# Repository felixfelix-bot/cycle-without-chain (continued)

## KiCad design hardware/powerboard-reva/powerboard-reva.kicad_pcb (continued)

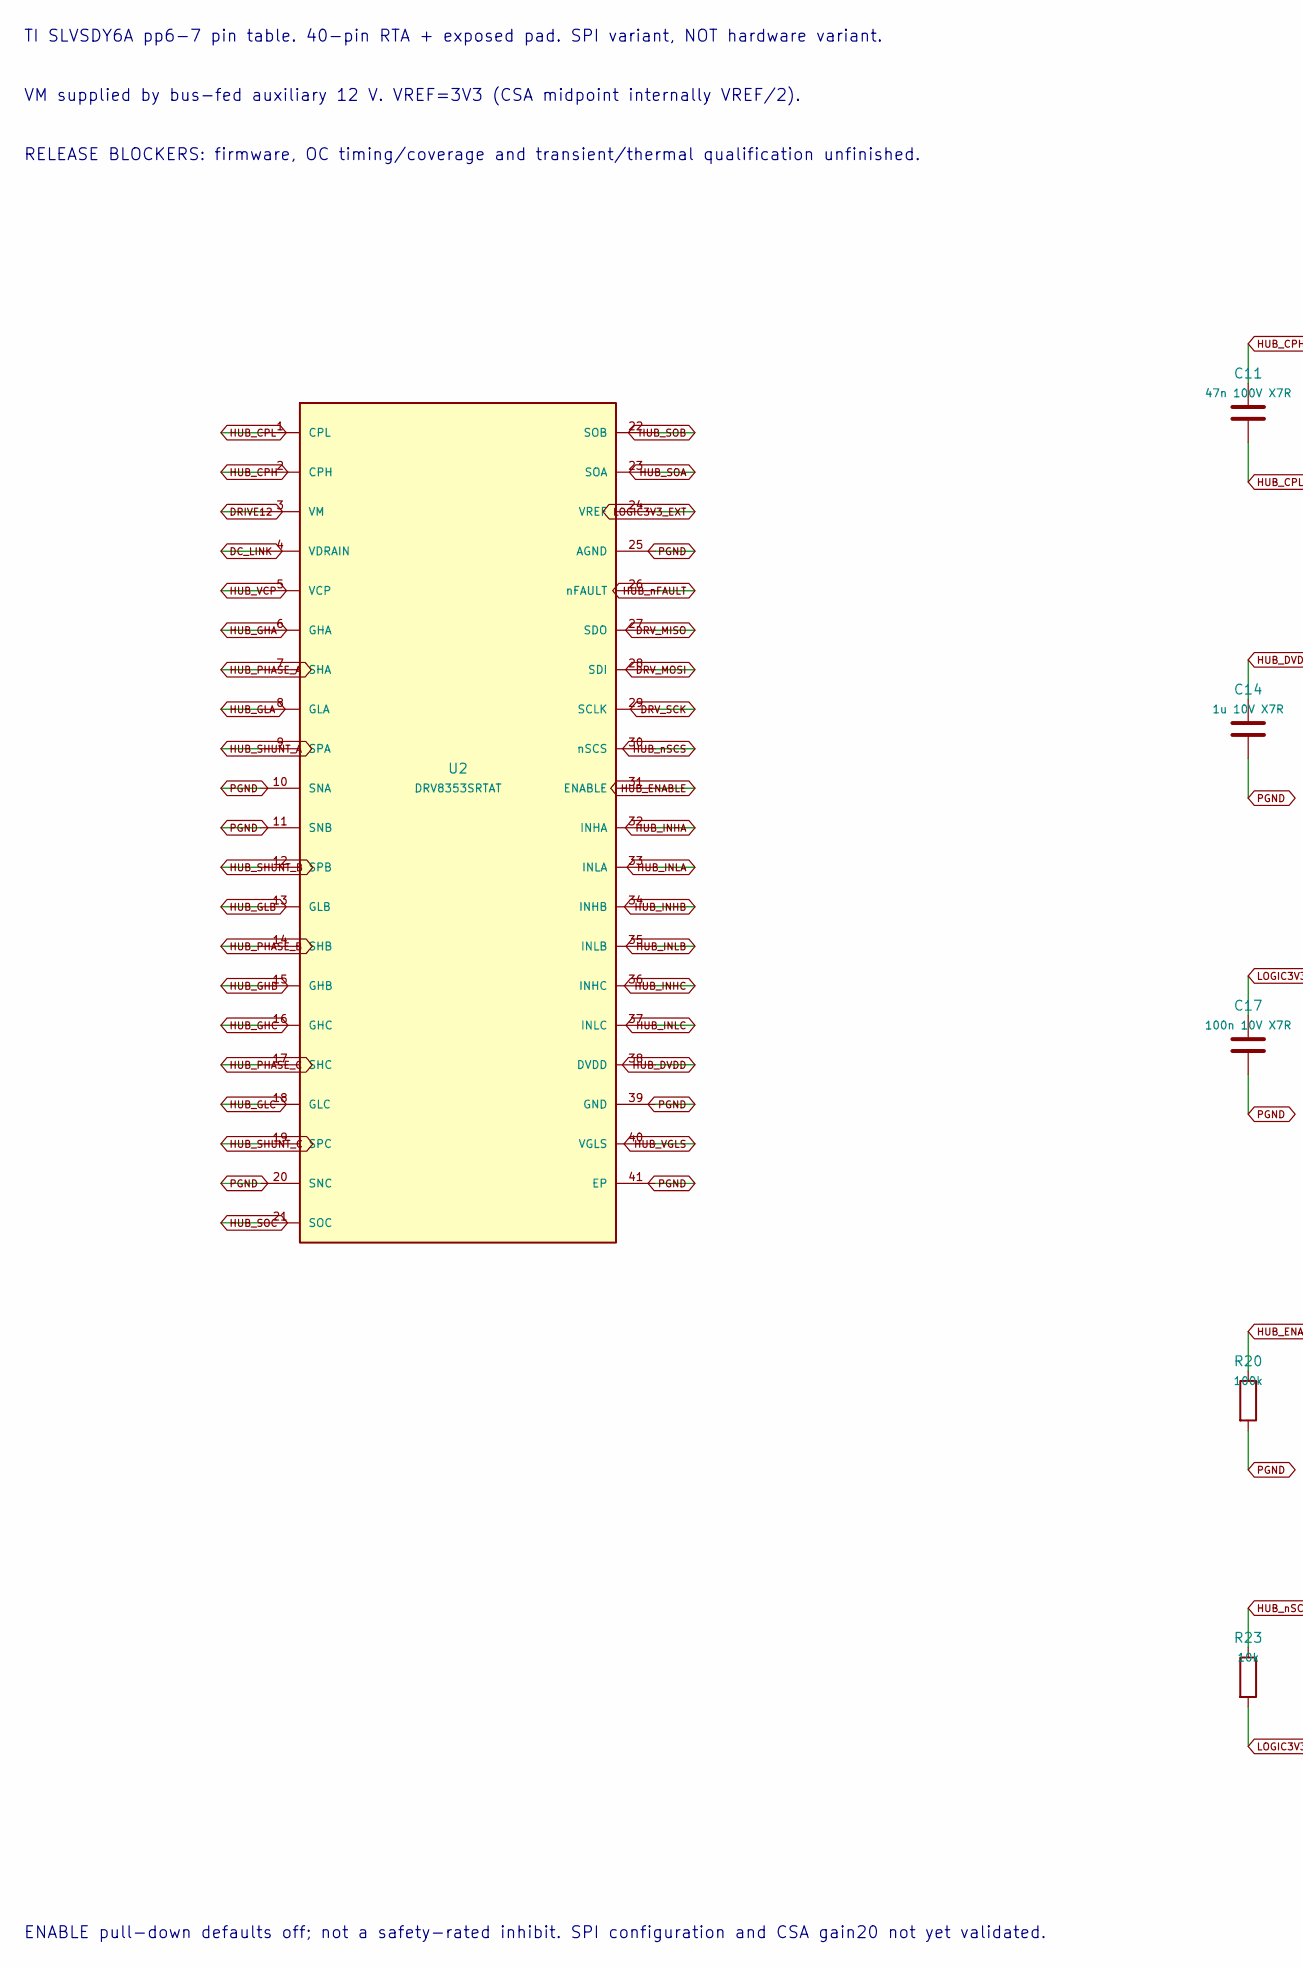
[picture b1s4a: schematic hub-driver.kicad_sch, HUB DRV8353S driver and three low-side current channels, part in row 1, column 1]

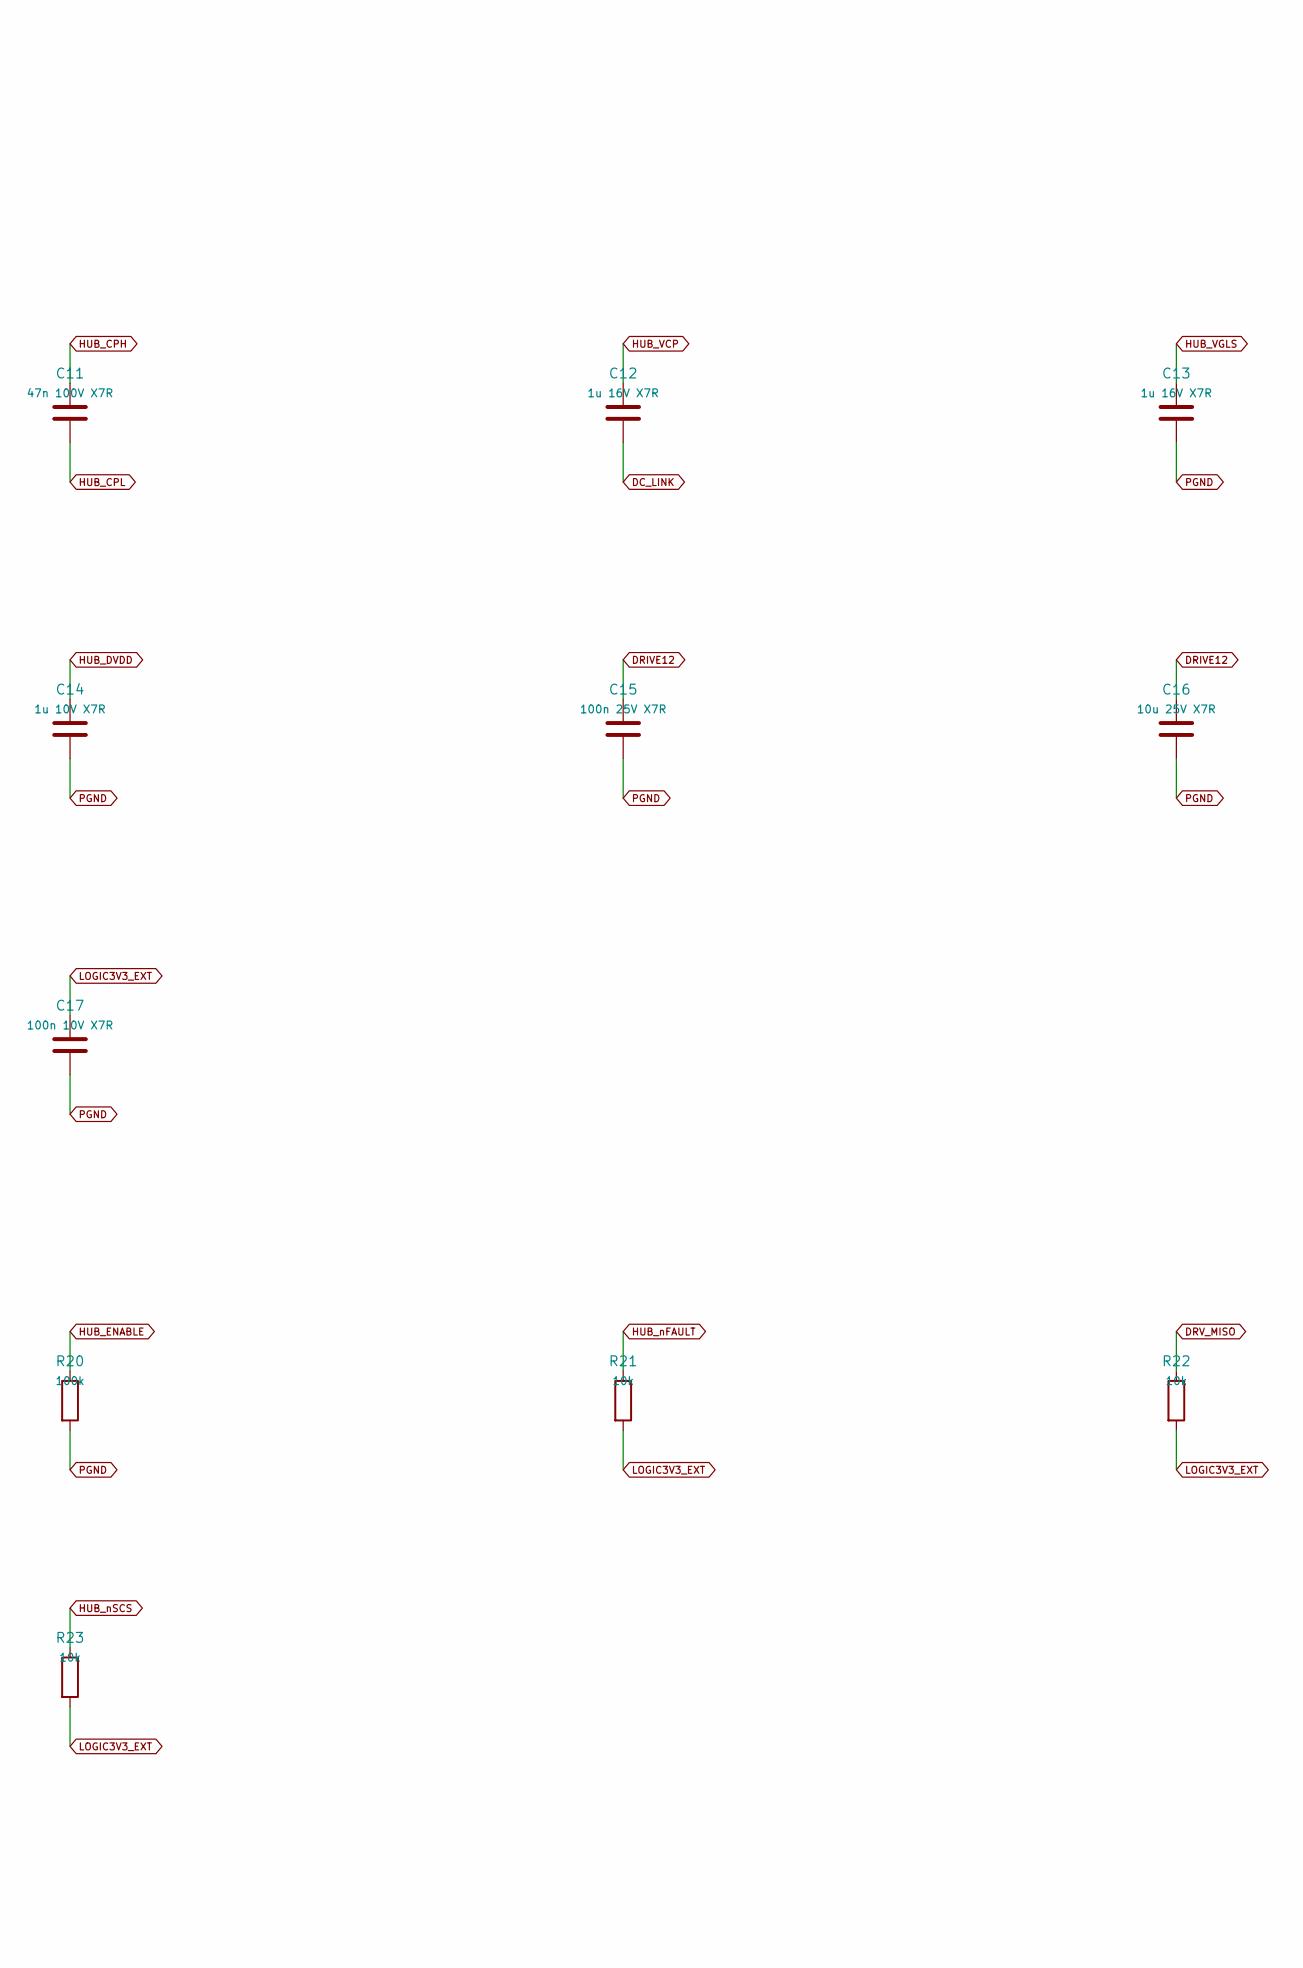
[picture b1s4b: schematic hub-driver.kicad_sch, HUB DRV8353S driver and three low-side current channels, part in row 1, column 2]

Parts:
C11: 47n 100V X7R; C_0805_2012Metric
C12, C13: 1u 16V X7R; C_0805_2012Metric
C14: 1u 10V X7R; C_0603_1608Metric
C15: 100n 25V X7R; C_0805_2012Metric
C16: 10u 25V X7R; C_0805_2012Metric
C17: 100n 10V X7R; C_0603_1608Metric
R20: 100k; R_0805_2012Metric
R21, R22, R23: 10k; R_0805_2012Metric
U2: DRV8353SRTAT; QFN-40-1EP_6x6mm_P0.5mm_EP4.6x4.6mm

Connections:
DC_LINK: C12.2, U2.4 (VDRAIN); also elsewhere on the board
DRIVE12: C15.1, C16.1, U2.3 (VM); also elsewhere on the board
DRV_MISO: R22.1, U2.27 (SDO); also elsewhere on the board
DRV_MOSI: U2.28 (SDI); also elsewhere on the board
DRV_SCK: U2.29 (SCLK); also elsewhere on the board
HUB_CPH: C11.1, U2.2 (CPH)
HUB_CPL: C11.2, U2.1 (CPL)
HUB_DVDD: C14.1, U2.38 (DVDD)
HUB_ENABLE: R20.1, U2.31 (ENABLE); also elsewhere on the board
HUB_GHA: U2.6 (GHA); also elsewhere on the board
HUB_GHB: U2.15 (GHB); also elsewhere on the board
HUB_GHC: U2.16 (GHC); also elsewhere on the board
HUB_GLA: U2.8 (GLA); also elsewhere on the board
HUB_GLB: U2.13 (GLB); also elsewhere on the board
HUB_GLC: U2.18 (GLC); also elsewhere on the board
HUB_INHA: U2.32 (INHA); also elsewhere on the board
HUB_INHB: U2.34 (INHB); also elsewhere on the board
HUB_INHC: U2.36 (INHC); also elsewhere on the board
HUB_INLA: U2.33 (INLA); also elsewhere on the board
HUB_INLB: U2.35 (INLB); also elsewhere on the board
HUB_INLC: U2.37 (INLC); also elsewhere on the board
HUB_PHASE_A: U2.7 (SHA); also elsewhere on the board
HUB_PHASE_B: U2.14 (SHB); also elsewhere on the board
HUB_PHASE_C: U2.17 (SHC); also elsewhere on the board
HUB_SHUNT_A: U2.9 (SPA); also elsewhere on the board
HUB_SHUNT_B: U2.12 (SPB); also elsewhere on the board
HUB_SHUNT_C: U2.19 (SPC); also elsewhere on the board
HUB_SOA: U2.23 (SOA); also elsewhere on the board
HUB_SOB: U2.22 (SOB); also elsewhere on the board
HUB_SOC: U2.21 (SOC); also elsewhere on the board
HUB_VCP: C12.1, U2.5 (VCP)
HUB_VGLS: C13.1, U2.40 (VGLS)
HUB_nFAULT: R21.1, U2.26 (nFAULT); also elsewhere on the board
HUB_nSCS: R23.1, U2.30 (nSCS); also elsewhere on the board
LOGIC3V3_EXT: C17.1, R21.2, R22.2, R23.2, U2.24 (VREF); also elsewhere on the board
PGND: C13.2, C14.2, C15.2, C16.2, C17.2, R20.2, U2.10 (SNA), U2.11 (SNB), U2.20 (SNC), U2.25 (AGND), U2.39 (GND), U2.41 (EP); also elsewhere on the board

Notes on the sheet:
TI SLVSDY6A pp6-7 pin table. 40-pin RTA + exposed pad. SPI variant, NOT hardware variant.
VM supplied by bus-fed auxiliary 12 V. VREF=3V3 (CSA midpoint internally VREF/2).
RELEASE BLOCKERS: firmware, OC timing/coverage and transient/thermal qualification unfinished.
ENABLE pull-down defaults off; not a safety-rated inhibit. SPI configuration and CSA gain20 not yet validated.

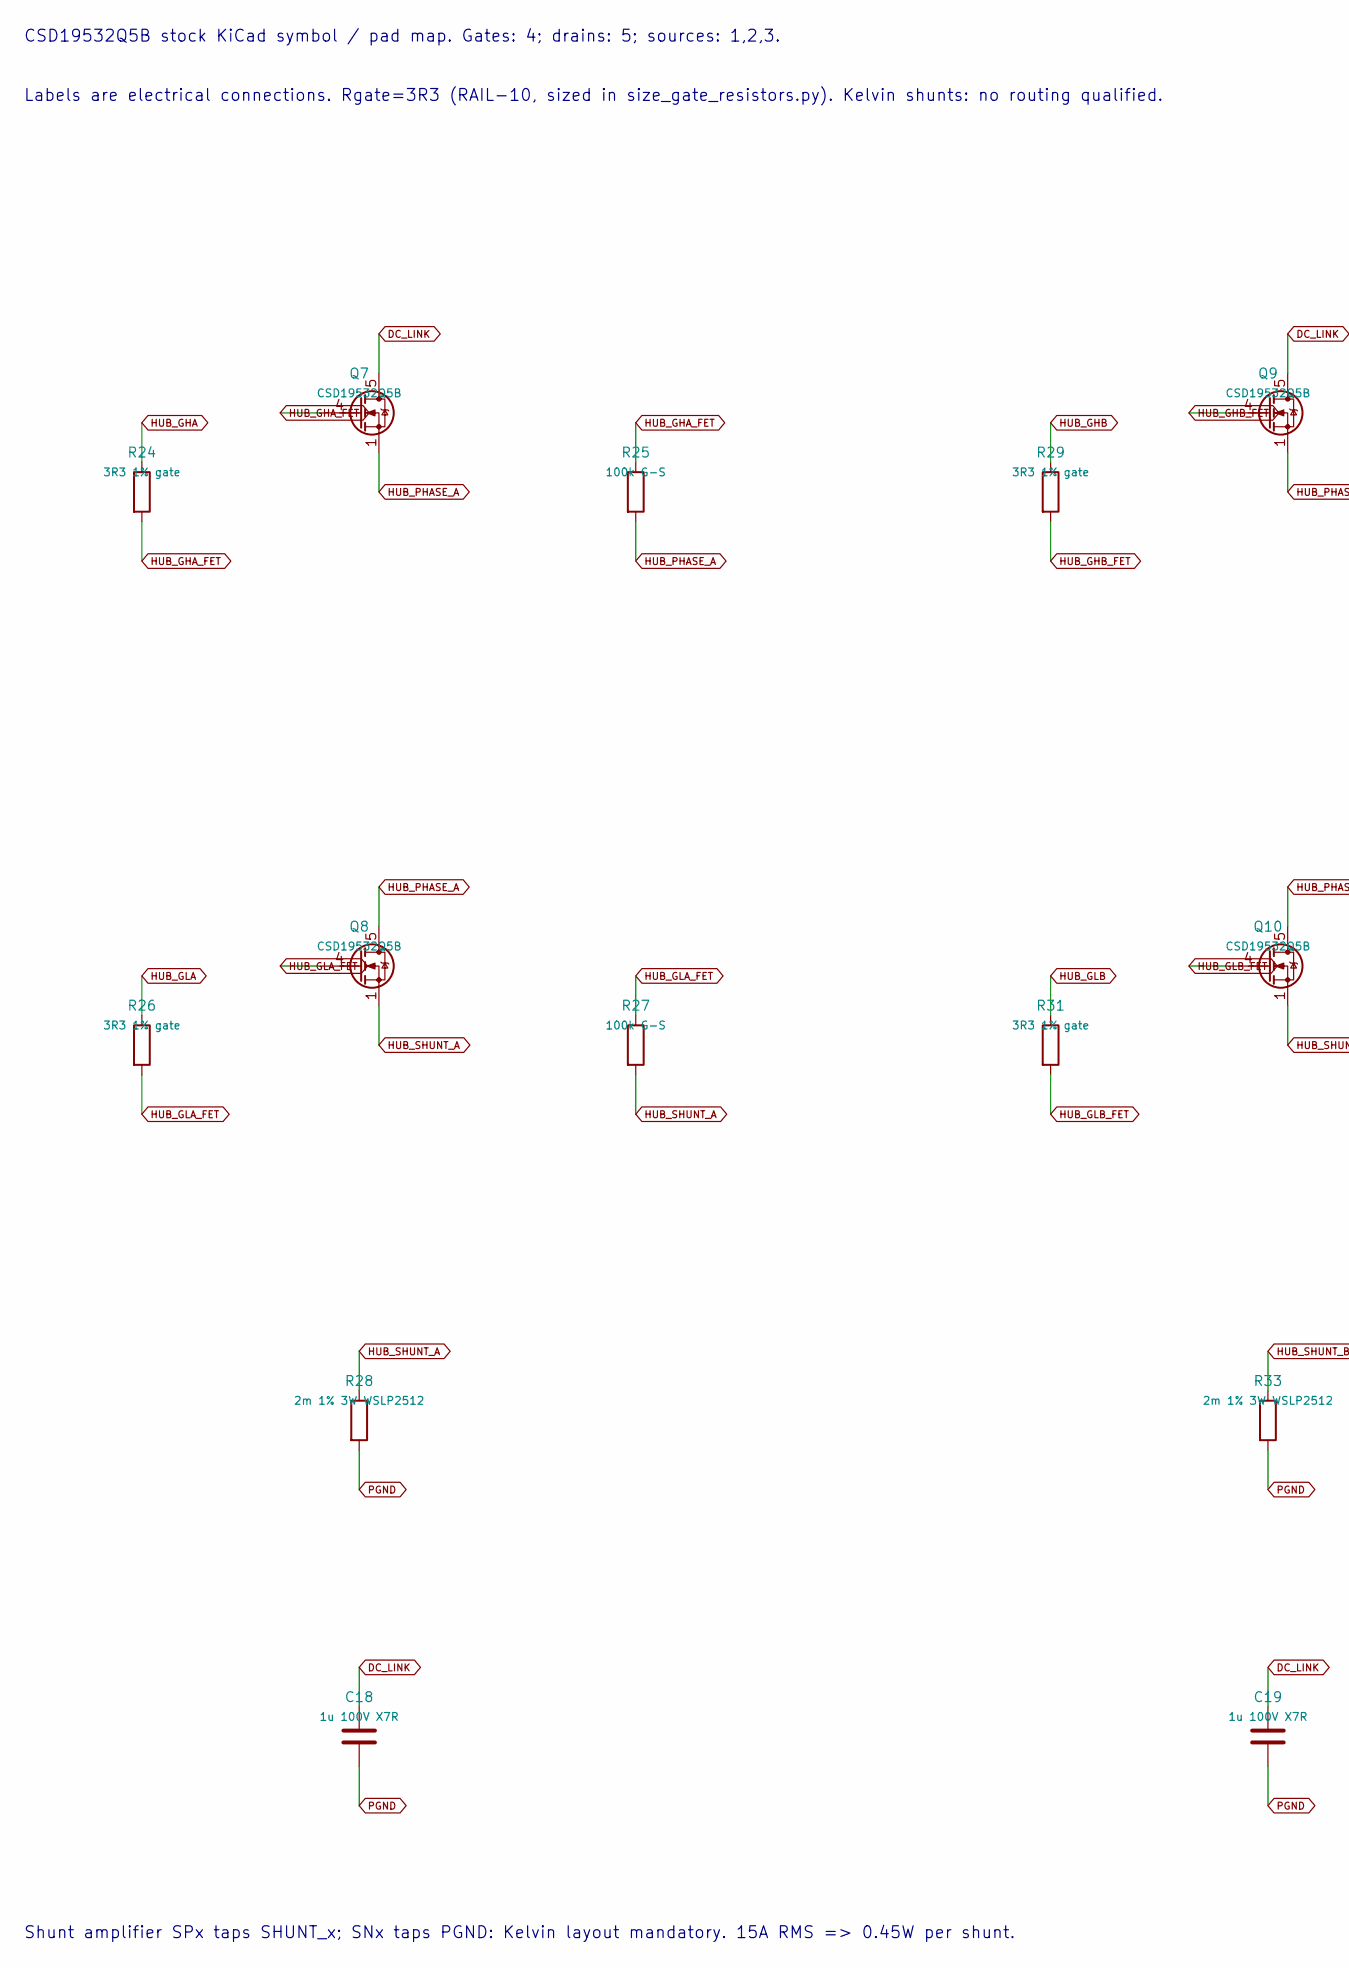
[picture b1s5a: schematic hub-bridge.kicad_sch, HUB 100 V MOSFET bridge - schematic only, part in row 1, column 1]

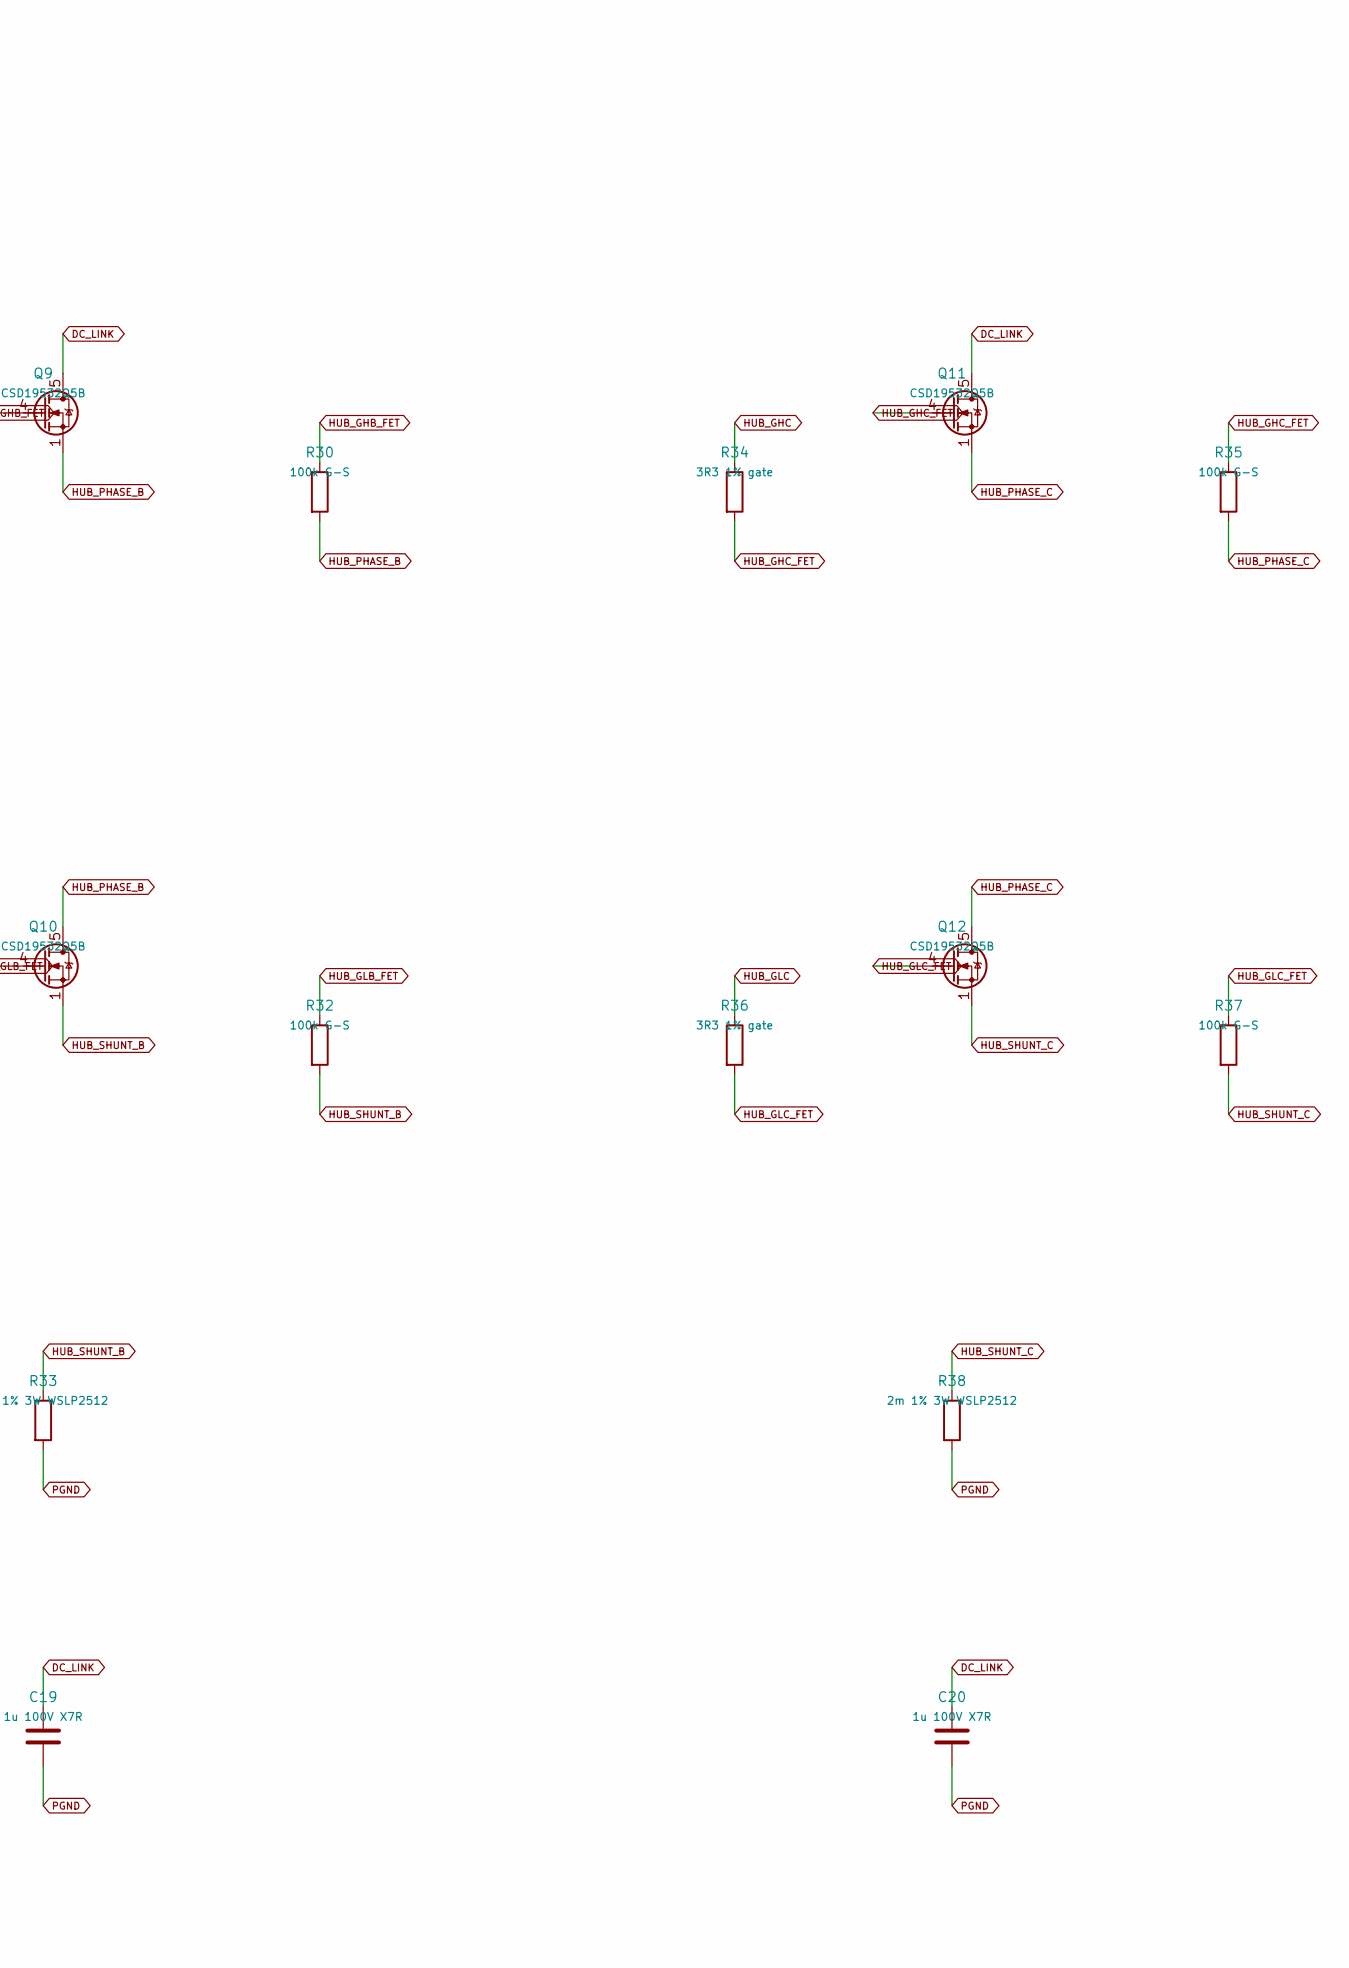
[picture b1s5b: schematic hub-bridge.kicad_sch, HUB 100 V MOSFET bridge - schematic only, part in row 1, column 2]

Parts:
C18, C19, C20: 1u 100V X7R; C_0805_2012Metric
Q7, Q8, Q9, Q10, Q11, Q12: CSD19532Q5B; TDSON-8-1
R24, R26, R29, R31, R34, R36: 3R3 1% gate; R_0805_2012Metric
R25, R27, R30, R32, R35, R37: 100k G-S; R_0805_2012Metric
R28, R33, R38: 2m 1% 3W WSLP2512; R_2512_6332Metric

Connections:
DC_LINK: C18.1, C19.1, C20.1, Q7.5 (D), Q9.5 (D), Q11.5 (D); also elsewhere on the board
HUB_GHA: R24.1; also elsewhere on the board
HUB_GHA_FET: Q7.4 (G), R24.2, R25.1
HUB_GHB: R29.1; also elsewhere on the board
HUB_GHB_FET: Q9.4 (G), R29.2, R30.1
HUB_GHC: R34.1; also elsewhere on the board
HUB_GHC_FET: Q11.4 (G), R34.2, R35.1
HUB_GLA: R26.1; also elsewhere on the board
HUB_GLA_FET: Q8.4 (G), R26.2, R27.1
HUB_GLB: R31.1; also elsewhere on the board
HUB_GLB_FET: Q10.4 (G), R31.2, R32.1
HUB_GLC: R36.1; also elsewhere on the board
HUB_GLC_FET: Q12.4 (G), R36.2, R37.1
HUB_PHASE_A: Q7.1 (S), Q7.2 (S), Q7.3 (S), Q8.5 (D), R25.2; also elsewhere on the board
HUB_PHASE_B: Q9.1 (S), Q9.2 (S), Q9.3 (S), Q10.5 (D), R30.2; also elsewhere on the board
HUB_PHASE_C: Q11.1 (S), Q11.2 (S), Q11.3 (S), Q12.5 (D), R35.2; also elsewhere on the board
HUB_SHUNT_A: Q8.1 (S), Q8.2 (S), Q8.3 (S), R27.2, R28.1; also elsewhere on the board
HUB_SHUNT_B: Q10.1 (S), Q10.2 (S), Q10.3 (S), R32.2, R33.1; also elsewhere on the board
HUB_SHUNT_C: Q12.1 (S), Q12.2 (S), Q12.3 (S), R37.2, R38.1; also elsewhere on the board
PGND: C18.2, C19.2, C20.2, R28.2, R33.2, R38.2; also elsewhere on the board

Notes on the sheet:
CSD19532Q5B stock KiCad symbol / pad map. Gates: 4; drains: 5; sources: 1,2,3.
Labels are electrical connections. Rgate=3R3 (RAIL-10, sized in size_gate_resistors.py). Kelvin shunts: no routing qualified.
Shunt amplifier SPx taps SHUNT_x; SNx taps PGND: Kelvin layout mandatory. 15A RMS => 0.45W per shunt.

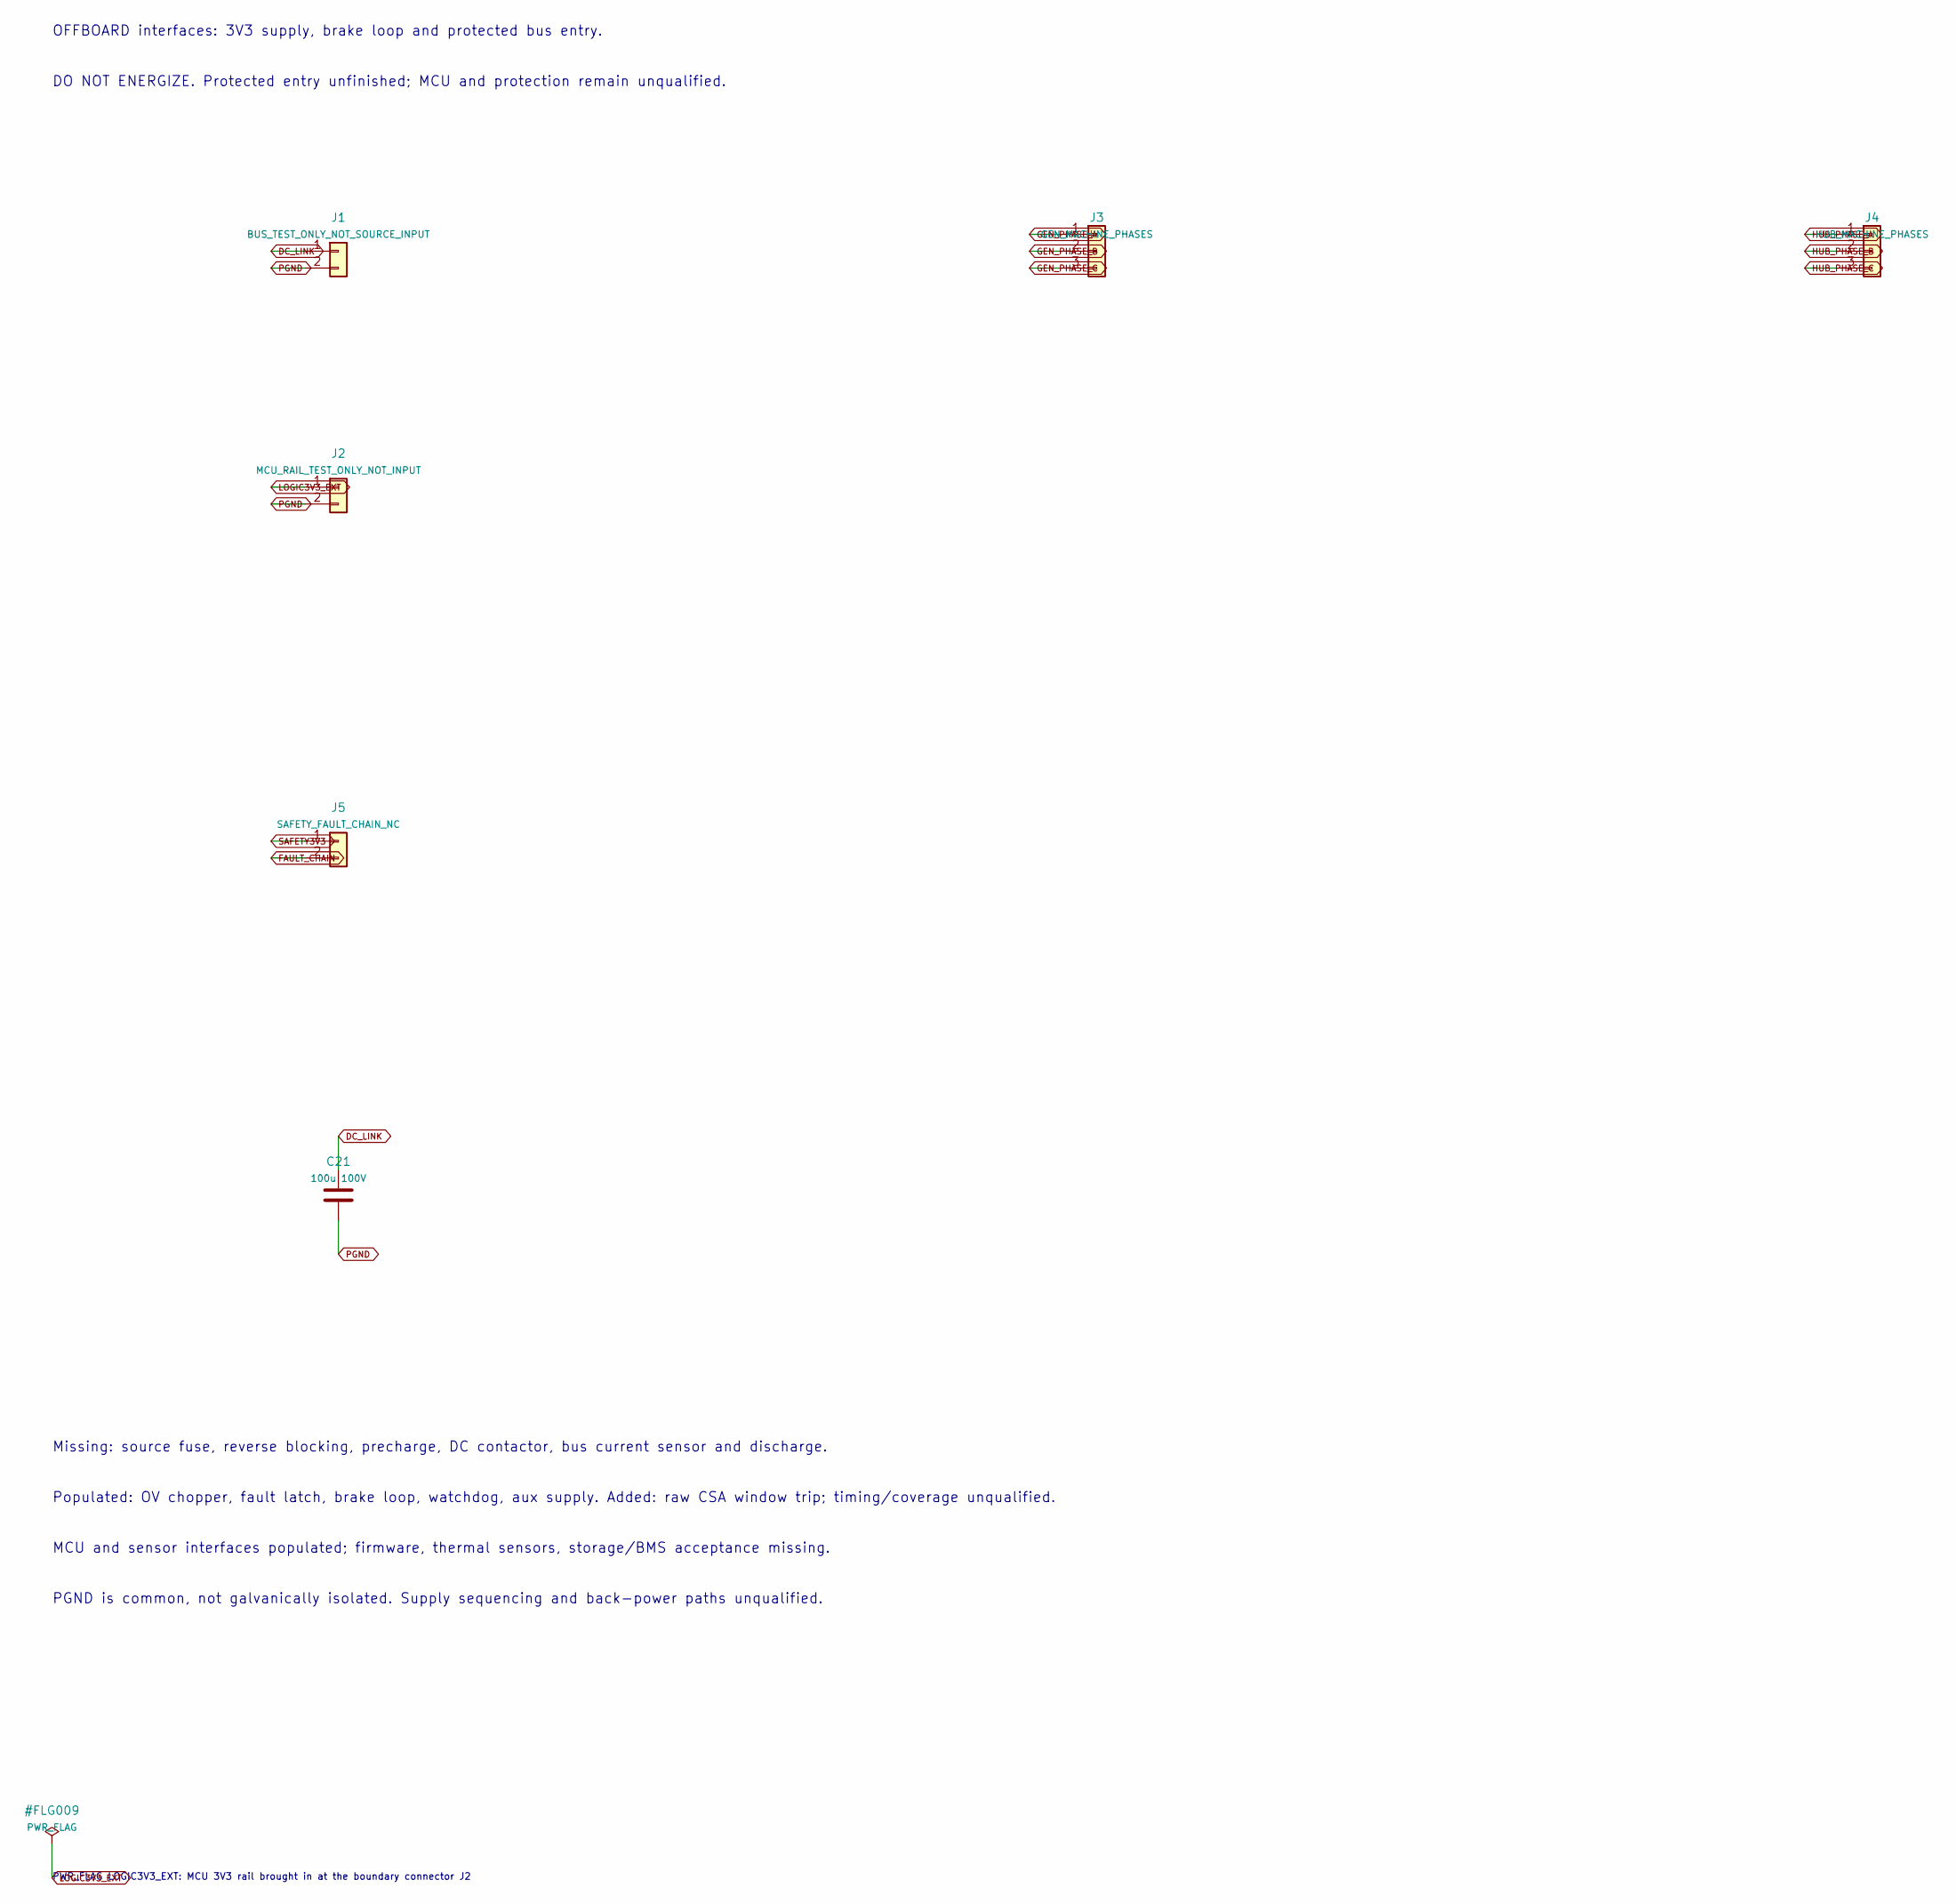
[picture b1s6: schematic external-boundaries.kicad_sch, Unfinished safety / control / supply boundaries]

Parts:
C21: 100u 100V; CP_Radial_D10.0mm_P5.00mm
J1: BUS_TEST_ONLY_NOT_SOURCE_INPUT; PinHeader_1x02_P2.54mm_Vertical
J2: MCU_RAIL_TEST_ONLY_NOT_INPUT; PinHeader_1x02_P2.54mm_Vertical
J3: GEN_MACHINE_PHASES; PinHeader_1x03_P2.54mm_Vertical
J4: HUB_MACHINE_PHASES; PinHeader_1x03_P2.54mm_Vertical
J5: SAFETY_FAULT_CHAIN_NC; PinHeader_1x02_P2.54mm_Vertical

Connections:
DC_LINK: C21.1, J1.1; also elsewhere on the board
FAULT_CHAIN: J5.2; also elsewhere on the board
GEN_PHASE_A: J3.1; also elsewhere on the board
GEN_PHASE_B: J3.2; also elsewhere on the board
GEN_PHASE_C: J3.3; also elsewhere on the board
HUB_PHASE_A: J4.1; also elsewhere on the board
HUB_PHASE_B: J4.2; also elsewhere on the board
HUB_PHASE_C: J4.3; also elsewhere on the board
LOGIC3V3_EXT: J2.1; also elsewhere on the board
PGND: C21.2, J1.2, J2.2; also elsewhere on the board
SAFETY3V3: J5.1; also elsewhere on the board

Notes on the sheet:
OFFBOARD interfaces: 3V3 supply, brake loop and protected bus entry.
DO NOT ENERGIZE. Protected entry unfinished; MCU and protection remain unqualified.
Missing: source fuse, reverse blocking, precharge, DC contactor, bus current sensor and discharge.
Populated: OV chopper, fault latch, brake loop, watchdog, aux supply. Added: raw CSA window trip; timing/coverage unqualified.
MCU and sensor interfaces populated; firmware, thermal sensors, storage/BMS acceptance missing.
PGND is common, not galvanically isolated. Supply sequencing and back-power paths unqualified.
PWR_FLAG LOGIC3V3_EXT: MCU 3V3 rail brought in at the boundary connector J2
